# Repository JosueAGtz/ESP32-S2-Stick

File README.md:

# ESP32-S2-Stick
It is a breadboard-compatible development board featuring the ESP32-S2 series of SoC, Xtensa® single-core 32-bit LX7 microprocessor 4 MB flash and optional 2 MB PSRAM in chip package 26 GPIOs, rich set of peripherals such as UART, SPI, I2C, TOUCH, DAC, ADC, and USB, a 2x2mm SK6812 RGB serial LED and a 0603 SMD blue LED. USB-C connector, castellated holes for low-profile integrations, and an onboard PCB antenna.

## ESP32-S2-Stick Dimensions

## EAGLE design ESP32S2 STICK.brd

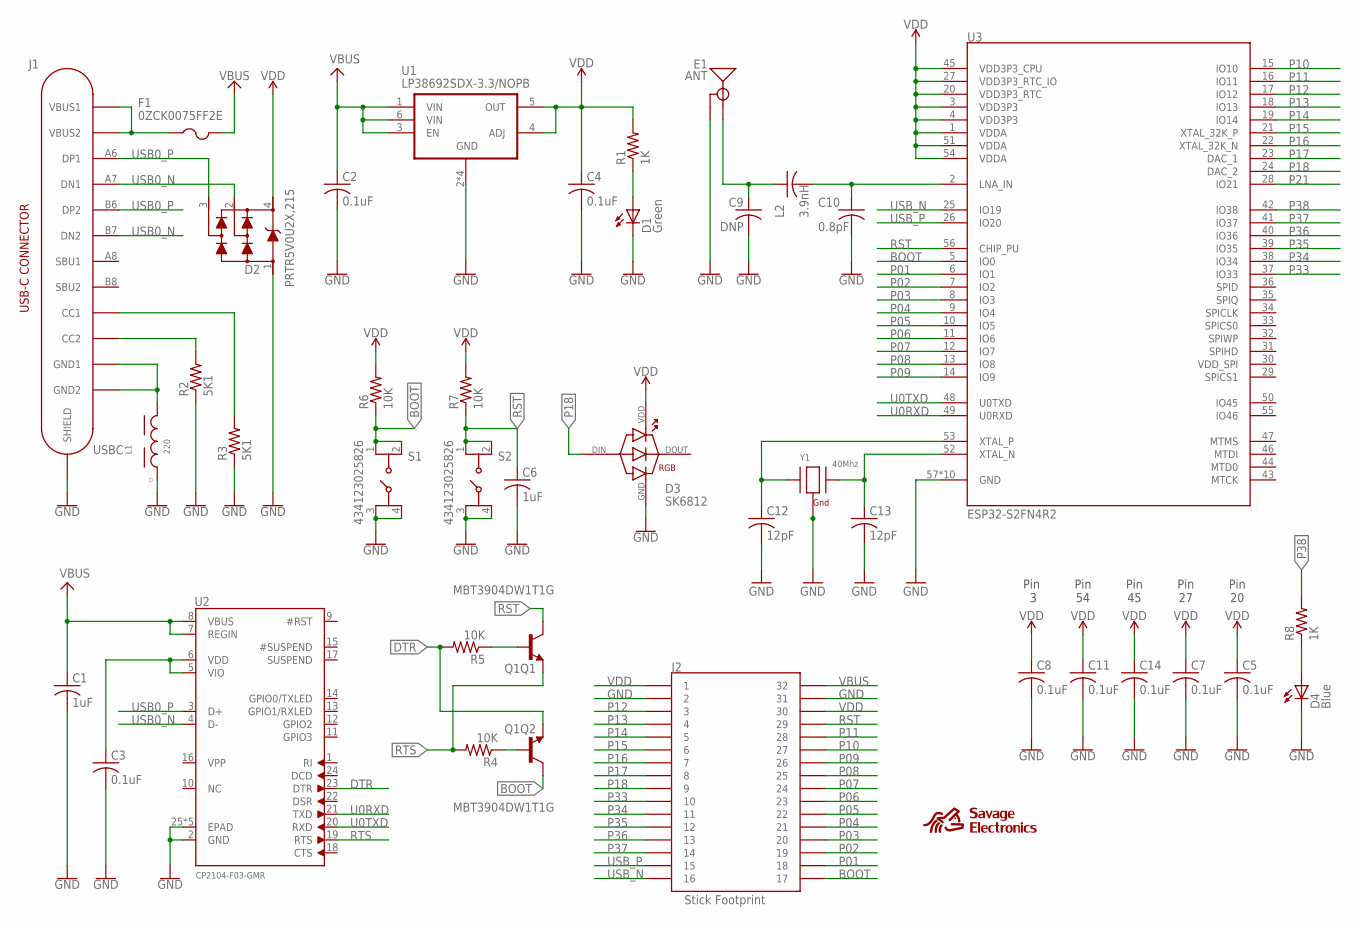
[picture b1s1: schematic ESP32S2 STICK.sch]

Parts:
C1, C6: 1uF; C0603
C2, C3, C4, C5, C7, C8, C11, C14: 0.1uF; C0603
C9: DNP; C0402
C10: 0.8pF; C0402
C12, C13: 12pF; C0402
D1: Green; CHIP-LED0603
D2: PRTR5V0U2X,215; SOT143B
D3: SK6812; 20X20
D4: Blue; CHIP-LED0603
E1: ANT; TRACE_ANTENNA_2.4GHZ_15.2MM
F1: 0ZCK0075FF2E; R0603F
J1: USBC
J2: Stick Footprint; NRF52832_CASTELLATED
L1: 220; WE-CBA_0603(W=2.2)
L2: 3.9nH; C0402
Q1: MBT3904DW1T1G; SC70-6
R1, R8: 1K; R0402
R2, R3: 5K1; R0402
R4, R5, R6, R7: 10K; R0402
S1, S2: 434123025826
U1: LP38692SDX-3.3/NOPB; LLP6-3X3
U2: CP2102N-A02-GQFN24R; QFN24_4MM_SMSC
U3: ESP32-S2FN4R2; QFN40P700X700X90-57T400N
Y1: 40Mhz; NX2016

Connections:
BOOT: J2.17AA (17), J2.17BB (17), J2.17CC (17), J2.P17DD (17), Q1.6 (C), R6.1, S1.1, S1.2, U3.5 (IO0)
DTR: Q1.1 (E), R5.2, U2.23 (DTR)
GND: C1.2, C2.2, C3.2, C4.2, C5.2, C6.2, C7.2, C8.2, C9.2, C10.2, C11.2, C12.2, C13.2, C14.2, D1.C, D2.1, D3.3 (GND), D4.C, E1.GND, J1.S1 (SHIELD), J1.S2 (SHIELD), J1.S3 (SHIELD), J1.S4 (SHIELD), J2.2, J2.2B (2), J2.2C (2), J2.29 (31), J2.29B (31), J2.29C (31), J2.P2 (2), J2.P29 (31), L1.1, R2.1, R3.1, S1.3, S1.4, S2.3, S2.4, U1.2 (GND), U1.P$1 (GND), U1.P$2 (GND), U1.P$3 (GND), U2.2 (GND), U2.25 (EPAD), U2.P$1 (EPAD), U2.P$2 (EPAD), U2.P$3 (EPAD), U2.P$4 (EPAD), U3.57 (GND), U3.P$1 (GND), U3.P$2 (GND), U3.P$3 (GND), U3.P$4 (GND), U3.P$5 (GND), U3.P$6 (GND), U3.P$7 (GND), U3.P$8 (GND), U3.P$9 (GND), Y1.2 (G2), Y1.4 (G1)
unnamed: J1.A1B12 (GND1), J1.B1A12 (GND2), L1.2
unnamed: D4.A, R8.1
unnamed: J1.B5 (CC2), R2.2
unnamed: J1.A5 (CC1), R3.2
unnamed: Q1.5 (B), R5.1
unnamed: C10.1, L2.2, U3.2 (LNA_IN)
unnamed: Q1.2 (B), R4.1
unnamed: C12.1, U3.53 (XTAL_P), Y1.1 (X1)
unnamed: C13.1, U3.52 (XTAL_N), Y1.3 (X2)
unnamed: D1.A, R1.1
unnamed: C9.1, E1.ANT (SIGNAL), L2.1
unnamed: C3.1, U2.5 (VIO), U2.6 (VDD)
P01: J2.16 (18), J2.16B (18), J2.16C (18), J2.P16 (18), U3.6 (IO1)
P02: J2.17 (19), J2.17B (19), J2.17C (19), J2.P17 (19), U3.7 (IO2)
P03: J2.18 (20), J2.18B (20), J2.18C (20), J2.P18 (20), U3.8 (IO3)
P04: J2.19 (21), J2.19B (21), J2.19C (21), J2.P19 (21), U3.9 (IO4)
P05: J2.20 (22), J2.20B (22), J2.20C (22), J2.P20 (22), U3.10 (IO5)
P06: J2.21 (23), J2.21B (23), J2.21C (23), J2.P21 (23), U3.11 (IO6)
P07: J2.22 (24), J2.22B (24), J2.22C (24), J2.P22 (24), U3.12 (IO7)
P08: J2.23 (25), J2.23B (25), J2.23C (25), J2.P23 (25), U3.13 (IO8)
P09: J2.24 (26), J2.24B (26), J2.24C (26), J2.P24 (26), U3.14 (IO9)
P10: J2.25 (27), J2.25B (27), J2.25C (27), J2.P25 (27), U3.15 (IO10)
P11: J2.26 (28), J2.26B (28), J2.26C (28), J2.P26 (28), U3.16 (IO11)
P12: J2.3, J2.3B (3), J2.3C (3), J2.P3 (3), U3.17 (IO12)
P13: J2.4, J2.4B (4), J2.4C (4), J2.P4 (4), U3.18 (IO13)
P14: J2.5, J2.5B (5), J2.5C (5), J2.P5 (5), U3.19 (IO14)
P15: J2.6, J2.6B (6), J2.6C (6), J2.P6 (6), U3.21 (XTAL_32K_P)
P16: J2.7, J2.7B (7), J2.7C (7), J2.P7 (7), U3.22 (XTAL_32K_N)
P17: J2.8, J2.8B (8), J2.8C (8), J2.P8 (8), U3.23 (DAC_1)
P18: D3.4 (DIN), J2.9, J2.9B (9), J2.9C (9), J2.P9 (9), U3.24 (DAC_2)
P21: U3.28 (IO21)
P33: J2.10, J2.10B (10), J2.10C (10), J2.P10 (10), U3.37 (IO33)
P34: J2.11, J2.11B (11), J2.11C (11), J2.P11 (11), U3.38 (IO34)
P35: J2.12, J2.12B (12), J2.12C (12), J2.P12 (12), U3.39 (IO35)
P36: J2.13, J2.13B (13), J2.13C (13), J2.P13 (13), U3.40 (IO36)
P37: J2.14, J2.14B (14), J2.14C (14), J2.P14 (14), U3.41 (IO37)
P38: R8.2, U3.42 (IO38)
RST: C6.1, J2.27 (29), J2.27B (29), J2.27C (29), J2.P27 (29), Q1.3 (C), R7.1, S2.1, S2.2, U3.56 (CHIP_PU)
RTS: Q1.4 (E), R4.2, U2.19 (RTS)
U0RXD: U2.21 (TXD), U3.49 (U0RXD)
U0TXD: U2.20 (RXD), U3.48 (U0TXD)
USB0_N: D2.2, J1.A7 (DN1), J1.B7 (DN2), U2.4 (D-)
USB0_P: D2.3, J1.A6 (DP1), J1.B6 (DP2), U2.3 (D+)
USB_N: J2.16AA (16), J2.16BB (16), J2.16CC (16), J2.P16A (16), U3.25 (IO19)
USB_P: J2.15, J2.15B (15), J2.15C (15), J2.P15 (15), U3.26 (IO20)
VBUS: C1.1, C2.1, F1.2, J2.30 (32), J2.30B (32), J2.30C (32), J2.P30 (32), U1.1 (VIN), U1.3 (EN), U1.6 (VIN), U2.7 (REGIN), U2.8 (VBUS)
VCC: F1.1, J1.A4B9 (VBUS1), J1.B4A9 (VBUS2)
VDD: C4.1, C5.1, C7.1, C8.1, C11.1, C14.1, D2.4, D3.1 (VDD), J2.1, J2.1B (1), J2.1C (1), J2.28 (30), J2.28B (30), J2.28C (30), J2.P1 (1), J2.P28 (30), R1.2, R6.2, R7.2, U1.4 (ADJ), U1.5 (OUT), U3.1 (VDDA), U3.3 (VDD3P3), U3.4 (VDD3P3), U3.20 (VDD3P3_RTC), U3.27 (VDD3P3_RTC_IO), U3.45 (VDD3P3_CPU), U3.51 (VDDA), U3.54 (VDDA)
VDD_SPI: U3.30 (VDD_SPI)

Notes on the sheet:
Pin 3
Pin 54
Pin 45
Pin 27
Pin 20

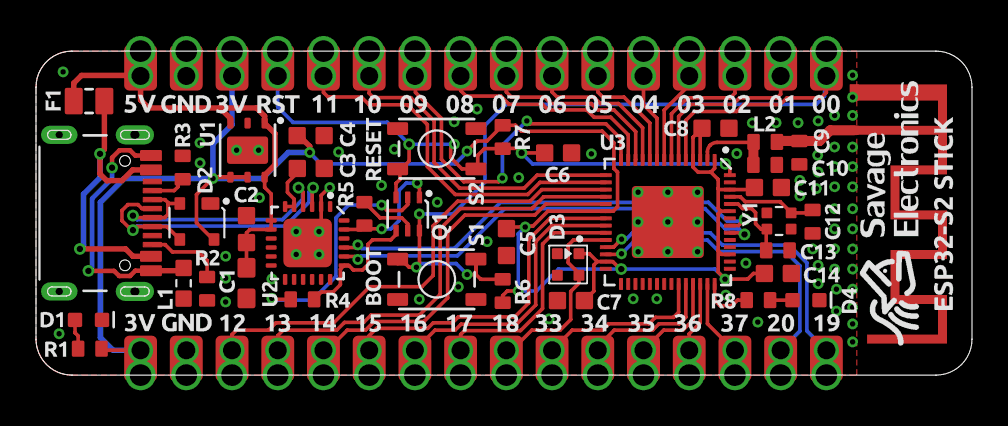
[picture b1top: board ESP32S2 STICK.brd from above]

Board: 2 copper layers, 52.0 x 18.0 mm, 39 parts (0 on the bottom side), 50 nets.

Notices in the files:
parts and their libraries:
EMCComponents: Copyright: Würth Elektronik
SparkFun-RF: Licensing: Creative Commons ShareAlike 4.0 International - https://creativecommons.org/licenses/by-sa/4.0
